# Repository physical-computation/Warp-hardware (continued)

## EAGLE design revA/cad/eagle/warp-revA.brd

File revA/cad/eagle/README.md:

Warp revision A, Eagle CAD files
=========================

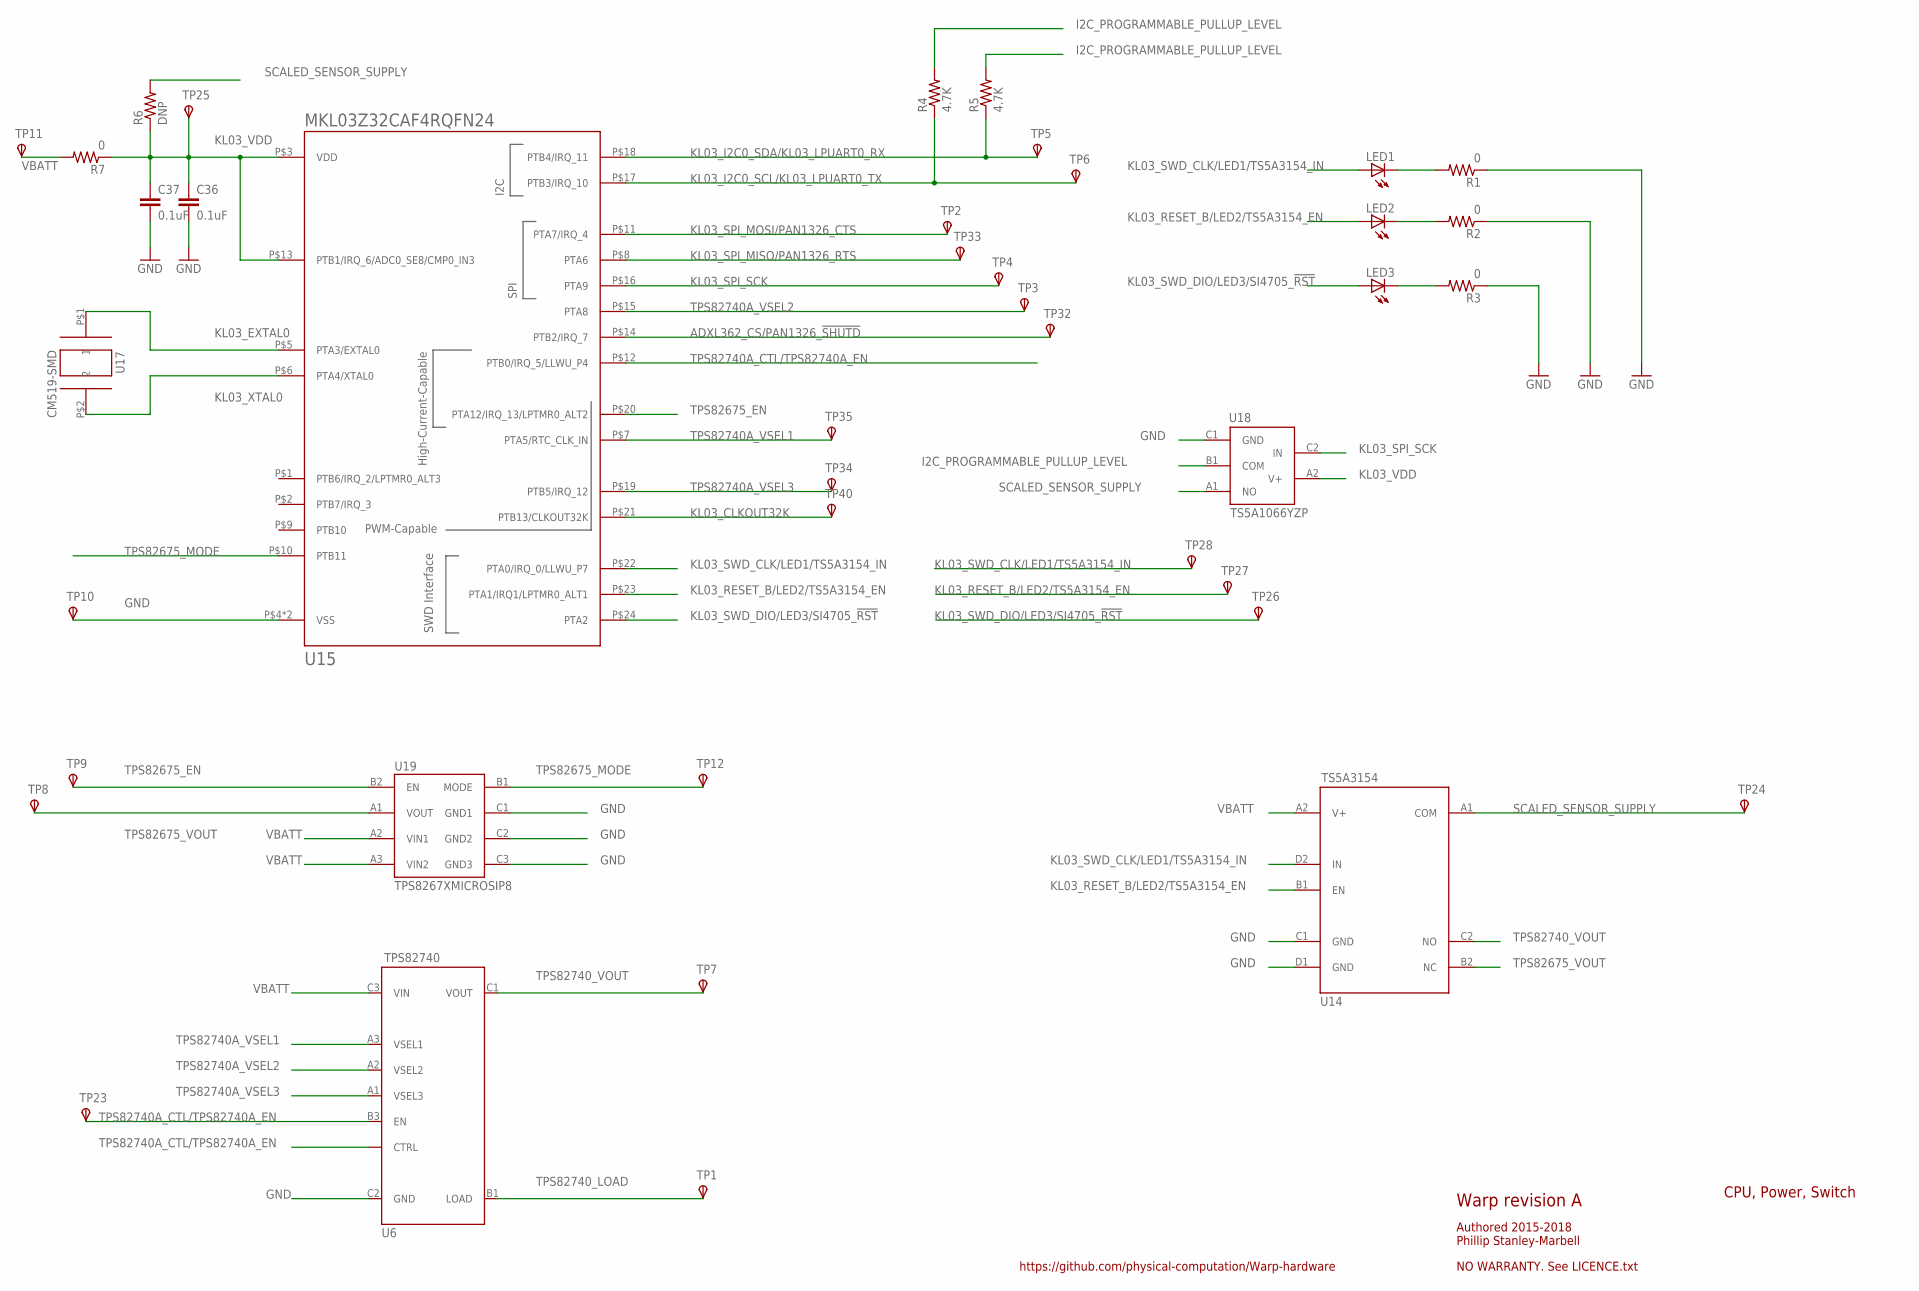
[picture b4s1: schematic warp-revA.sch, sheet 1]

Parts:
C36, C37: 0.1uF; 0402-CAP
LED1, LED2, LED3: LEDSML0603; SML0603
R1, R2, R3, R7: 0; 0402-RES
R4, R5: 4.7K; 0402-RES
R6: DNP; 0402-RES
TP1, TP2, TP3, TP4, TP5, TP6, TP7, TP8, TP9, TP10, TP11, TP12, TP23, TP24, TP25, TP26, TP27, TP28, TP32, TP33, TP34, TP35, TP40: TPSTP06R; TP06R
U6: TPS82740
U14: TS5A3154
U15: MKL03Z32CAF4RQFN24; MKL03Z32VFK4R
U17: CM519-SMD; CM519
U18: TS5A1066YZP; R-XBGA-N5
U19: TPS8267XMICROSIP8; MICROSIP-8

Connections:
ADXL362_CS/PAN1326_!SHUTD: TP32.TP, U15.P$14 (PTB2/IRQ_7); also elsewhere on the board
GND: C36.2, C37.2, R1.1, R2.1, R3.1, TP10.TP, U6.C2 (GND), U14.C1 (GND), U14.D1 (GND), U15.P$4 (VSS), U15.P$PAD (VSS), U18.C1 (GND), U19.C1 (GND1), U19.C2 (GND2), U19.C3 (GND3); also elsewhere on the board
I2C_PROGRAMMABLE_PULLUP_LEVEL: R4.2, R5.2, U18.B1 (COM)
KL03_CLKOUT32K: TP40.TP, U15.P$21 (PTB13/CLKOUT32K); also elsewhere on the board
KL03_EXTAL0: U15.P$5 (PTA3/EXTAL0), U17.P$1 (1)
KL03_I2C0_SCL/KL03_LPUART0_TX: R4.1, TP6.TP, U15.P$17 (PTB3/IRQ_10); also elsewhere on the board
KL03_I2C0_SDA/KL03_LPUART0_RX: R5.1, TP5.TP, U15.P$18 (PTB4/IRQ_11); also elsewhere on the board
KL03_RESET_B/LED2/TS5A3154_EN: LED2.A, TP27.TP, U14.B1 (EN), U15.P$23 (PTA1/IRQ1/LPTMR0_ALT1); also elsewhere on the board
KL03_SPI_MISO/PAN1326_RTS: TP33.TP, U15.P$8 (PTA6); also elsewhere on the board
KL03_SPI_MOSI/PAN1326_CTS: TP2.TP, U15.P$11 (PTA7/IRQ_4); also elsewhere on the board
KL03_SPI_SCK: TP4.TP, U15.P$16 (PTA9), U18.C2 (IN); also elsewhere on the board
KL03_SWD_CLK/LED1/TS5A3154_IN: LED1.A, TP28.TP, U14.D2 (IN), U15.P$22 (PTA0/IRQ_0/LLWU_P7); also elsewhere on the board
KL03_SWD_DIO/LED3/SI4705_!RST: LED3.A, TP26.TP, U15.P$24 (PTA2); also elsewhere on the board
KL03_VDD: C36.1, C37.1, R6.1, R7.1, TP25.TP, U15.P$3 (VDD), U15.P$13 (PTB1/IRQ_6/ADC0_SE8/CMP0_IN3), U18.A2 (V+)
KL03_XTAL0: U15.P$6 (PTA4/XTAL0), U17.P$2 (2)
unnamed: LED1.C, R1.2
unnamed: LED2.C, R2.2
unnamed: LED3.C, R3.2
SCALED_SENSOR_SUPPLY: R6.2, TP24.TP, U14.A1 (COM), U18.A1 (NO); also elsewhere on the board
TPS82675_EN: TP9.TP, U15.P$20 (PTA12/IRQ_13/LPTMR0_ALT2), U19.B2 (EN)
TPS82675_MODE: TP12.TP, U15.P$10 (PTB11), U19.B1 (MODE)
TPS82675_VOUT: TP8.TP, U14.B2 (NC), U19.A1 (VOUT)
TPS82740A_CTL/TPS82740A_EN: TP23.TP, U6.B2 (CTRL), U6.B3 (EN), U15.P$12 (PTB0/IRQ_5/LLWU_P4)
TPS82740A_VSEL1: TP35.TP, U6.A3 (VSEL1), U15.P$7 (PTA5/RTC_CLK_IN)
TPS82740A_VSEL2: TP3.TP, U6.A2 (VSEL2), U15.P$15 (PTA8)
TPS82740A_VSEL3: TP34.TP, U6.A1 (VSEL3), U15.P$19 (PTB5/IRQ_12)
TPS82740_LOAD: TP1.TP, U6.B1 (LOAD)
TPS82740_VOUT: TP7.TP, U6.C1 (VOUT), U14.C2 (NO)
VBATT: R7.2, TP11.TP, U6.C3 (VIN), U14.A2 (V+), U19.A2 (VIN1), U19.A3 (VIN2); also elsewhere on the board

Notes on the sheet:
Warp revision A
Authored 2015-2018 Phillip Stanley-Marbell
NO WARRANTY. See LICENCE.txt
https://github.com/physical-computation/Warp-hardware
CPU, Power, Switch

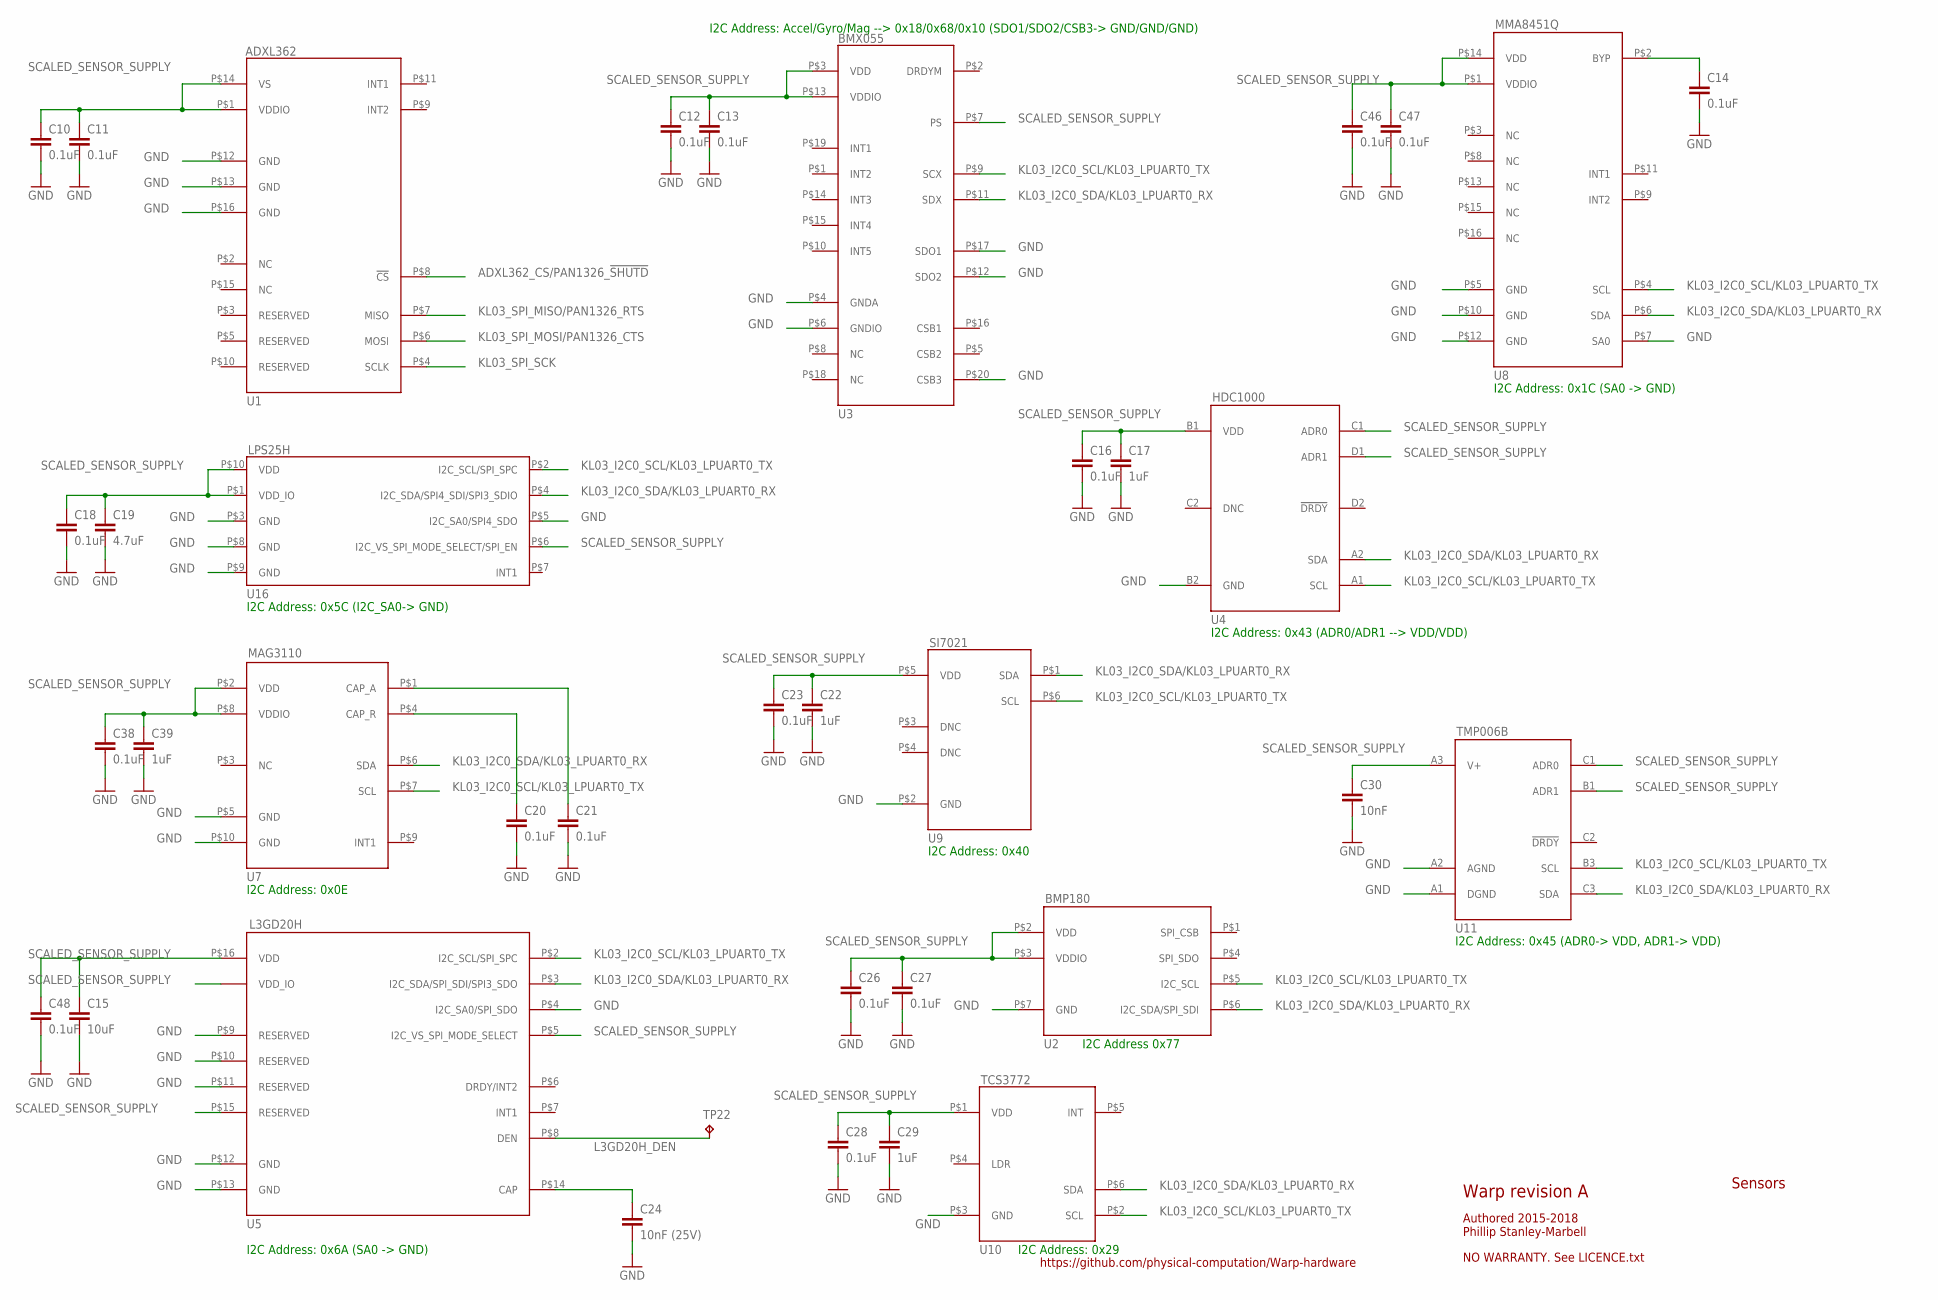
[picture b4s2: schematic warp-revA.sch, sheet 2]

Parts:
C10, C11, C12, C13, C14, C16, C18, C20, C21, C23, C26, C27, C28, C38, C46, C47, C48: 0.1uF; 0402-CAP
C15: 10uF; 0402-CAP
C17, C22, C29, C39: 1uF; 0402-CAP
C19: 4.7uF; 0402-CAP
C24: 10nF (25V); 0402-CAP
C30: 10nF; 0402-CAP
TP22: TPTP06R; TP06R
U1: ADXL362
U2: BMP180
U3: BMX055
U4: HDC1000
U5: L3GD20H
U7: MAG3110
U8: MMA8451Q
U9: SI7021
U10: TCS3772
U11: TMP006B
U16: LPS25H

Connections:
ADXL362_CS/PAN1326_!SHUTD: U1.P$8 (!CS); also elsewhere on the board
GND: C10.2, C11.2, C12.2, C13.2, C14.2, C15.2, C16.2, C17.2, C18.2, C19.2, C20.2, C21.2, C22.2, C23.2, C24.2, C26.2, C27.2, C28.2, C29.2, C30.2, C38.2, C39.2, C46.2, C47.2, C48.2, U1.P$12 (GND), U1.P$13 (GND), U1.P$16 (GND), U2.P$7 (GND), U3.P$4 (GNDA), U3.P$6 (GNDIO), U3.P$12 (SDO2), U3.P$17 (SDO1), U3.P$20 (CSB3), U4.B2 (GND), U5.P$4 (I2C_SA0/SPI_SDO), U5.P$9 (RESERVED), U5.P$10 (RESERVED), U5.P$11 (RESERVED), U5.P$12 (GND), U5.P$13 (GND), U7.P$5 (GND), U7.P$10 (GND), U8.P$5 (GND), U8.P$7 (SA0), U8.P$10 (GND), U8.P$12 (GND), U9.P$2 (GND), U10.P$3 (GND), U11.A1 (DGND), U11.A2 (AGND), U16.P$3 (GND), U16.P$5 (I2C_SA0/SPI4_SDO), U16.P$8 (GND), U16.P$9 (GND); also elsewhere on the board
KL03_I2C0_SCL/KL03_LPUART0_TX: U2.P$5 (I2C_SCL), U3.P$9 (SCX), U4.A1 (SCL), U5.P$2 (I2C_SCL/SPI_SPC), U7.P$7 (SCL), U8.P$4 (SCL), U9.P$6 (SCL), U10.P$2 (SCL), U11.B3 (SCL), U16.P$2 (I2C_SCL/SPI_SPC); also elsewhere on the board
KL03_I2C0_SDA/KL03_LPUART0_RX: U2.P$6 (I2C_SDA/SPI_SDI), U3.P$11 (SDX), U4.A2 (SDA), U5.P$3 (I2C_SDA/SPI_SDI/SPI3_SDO), U7.P$6 (SDA), U8.P$6 (SDA), U9.P$1 (SDA), U10.P$6 (SDA), U11.C3 (SDA), U16.P$4 (I2C_SDA/SPI4_SDI/SPI3_SDIO); also elsewhere on the board
KL03_SPI_MISO/PAN1326_RTS: U1.P$7 (MISO); also elsewhere on the board
KL03_SPI_MOSI/PAN1326_CTS: U1.P$6 (MOSI); also elsewhere on the board
KL03_SPI_SCK: U1.P$4 (SCLK); also elsewhere on the board
L3GD20H_DEN: TP22.TP, U5.P$8 (DEN)
unnamed: C14.1, U8.P$2 (BYP)
unnamed: C21.1, U7.P$1 (CAP_A)
unnamed: C20.1, U7.P$4 (CAP_R)
unnamed: C24.1, U5.P$14 (CAP)
SCALED_SENSOR_SUPPLY: C10.1, C11.1, C12.1, C13.1, C15.1, C16.1, C17.1, C18.1, C19.1, C22.1, C23.1, C26.1, C27.1, C28.1, C29.1, C30.1, C38.1, C39.1, C46.1, C47.1, C48.1, U1.P$1 (VDDIO), U1.P$14 (VS), U2.P$2 (VDD), U2.P$3 (VDDIO), U3.P$3 (VDD), U3.P$7 (PS), U3.P$13 (VDDIO), U4.B1 (VDD), U4.C1 (ADR0), U4.D1 (ADR1), U5.P$1 (VDD_IO), U5.P$5 (I2C_VS_SPI_MODE_SELECT), U5.P$15 (RESERVED), U5.P$16 (VDD), U7.P$2 (VDD), U7.P$8 (VDDIO), U8.P$1 (VDDIO), U8.P$14 (VDD), U9.P$5 (VDD), U10.P$1 (VDD), U11.A3 (V+), U11.B1 (ADR1), U11.C1 (ADR0), U16.P$1 (VDD_IO), U16.P$6 (I2C_VS_SPI_MODE_SELECT/SPI_EN), U16.P$10 (VDD); also elsewhere on the board

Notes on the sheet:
I2C Address: 0x1C (SA0 -> GND)
I2C Address: Accel/Gyro/Mag --> 0x18/0x68/0x10 (SDO1/SDO2/CSB3-> GND/GND/GND)
I2C Address: 0x43 (ADR0/ADR1 --> VDD/VDD)
I2C Address: 0x5C (I2C_SA0-> GND)
I2C Address: 0x0E
I2C Address: 0x40
I2C Address: 0x6A (SA0 -> GND)
I2C Address 0x77
I2C Address: 0x29
I2C Address: 0x45 (ADR0-> VDD, ADR1-> VDD)
Warp revision A
Authored 2015-2018 Phillip Stanley-Marbell
NO WARRANTY. See LICENCE.txt
https://github.com/physical-computation/Warp-hardware
Sensors

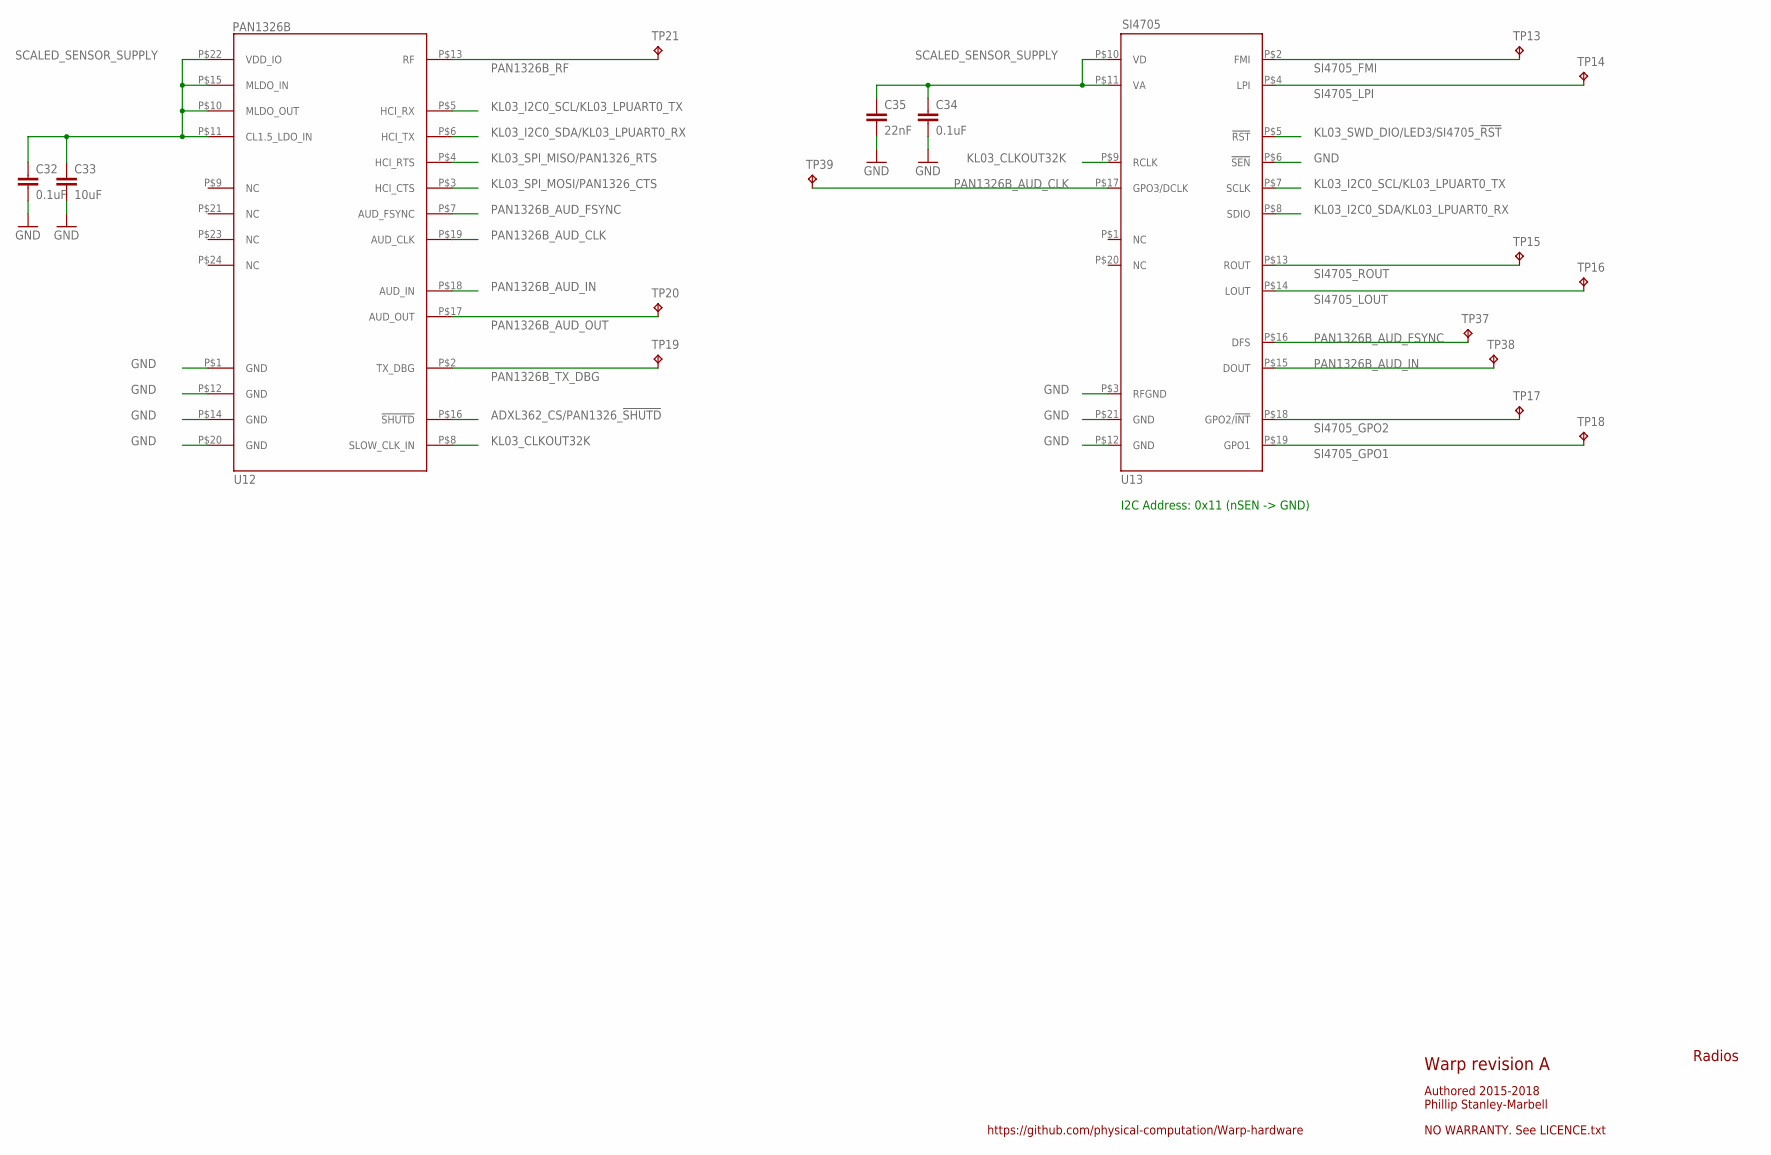
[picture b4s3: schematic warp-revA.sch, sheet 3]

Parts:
C32, C34: 0.1uF; 0402-CAP
C33: 10uF; 0402-CAP
C35: 22nF; 0402-CAP
TP13, TP14, TP15, TP16, TP17, TP18, TP19, TP20, TP21, TP37, TP38, TP39: TPTP06R; TP06R
U12: PAN1326B
U13: SI4705

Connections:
ADXL362_CS/PAN1326_!SHUTD: U12.P$16 (!SHUTD); also elsewhere on the board
GND: C32.2, C33.2, C34.2, C35.2, U12.P$1 (GND), U12.P$12 (GND), U12.P$14 (GND), U12.P$20 (GND), U13.P$3 (RFGND), U13.P$6 (!SEN), U13.P$12 (GND), U13.P$21 (GND); also elsewhere on the board
KL03_CLKOUT32K: U12.P$8 (SLOW_CLK_IN), U13.P$9 (RCLK); also elsewhere on the board
KL03_I2C0_SCL/KL03_LPUART0_TX: U12.P$5 (HCI_RX), U13.P$7 (SCLK); also elsewhere on the board
KL03_I2C0_SDA/KL03_LPUART0_RX: U12.P$6 (HCI_TX), U13.P$8 (SDIO); also elsewhere on the board
KL03_SPI_MISO/PAN1326_RTS: U12.P$4 (HCI_RTS); also elsewhere on the board
KL03_SPI_MOSI/PAN1326_CTS: U12.P$3 (HCI_CTS); also elsewhere on the board
KL03_SWD_DIO/LED3/SI4705_!RST: U13.P$5 (!RST); also elsewhere on the board
PAN1326B_AUD_CLK: TP39.TP, U12.P$19 (AUD_CLK), U13.P$17 (GPO3/DCLK)
PAN1326B_AUD_FSYNC: TP37.TP, U12.P$7 (AUD_FSYNC), U13.P$16 (DFS)
PAN1326B_AUD_IN: TP38.TP, U12.P$18 (AUD_IN), U13.P$15 (DOUT)
PAN1326B_AUD_OUT: TP20.TP, U12.P$17 (AUD_OUT)
PAN1326B_RF: TP21.TP, U12.P$13 (RF)
PAN1326B_TX_DBG: TP19.TP, U12.P$2 (TX_DBG)
SCALED_SENSOR_SUPPLY: C32.1, C33.1, C34.1, C35.1, U12.P$10 (MLDO_OUT), U12.P$11 (CL1.5_LDO_IN), U12.P$15 (MLDO_IN), U12.P$22 (VDD_IO), U13.P$10 (VD), U13.P$11 (VA); also elsewhere on the board
SI4705_FMI: TP13.TP, U13.P$2 (FMI)
SI4705_GPO1: TP18.TP, U13.P$19 (GPO1)
SI4705_GPO2: TP17.TP, U13.P$18 (GPO2/!INT)
SI4705_LOUT: TP16.TP, U13.P$14 (LOUT)
SI4705_LPI: TP14.TP, U13.P$4 (LPI)
SI4705_ROUT: TP15.TP, U13.P$13 (ROUT)

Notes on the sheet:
I2C Address: 0x11 (nSEN -> GND)
Warp revision A
Authored 2015-2018 Phillip Stanley-Marbell
NO WARRANTY. See LICENCE.txt
https://github.com/physical-computation/Warp-hardware
Radios

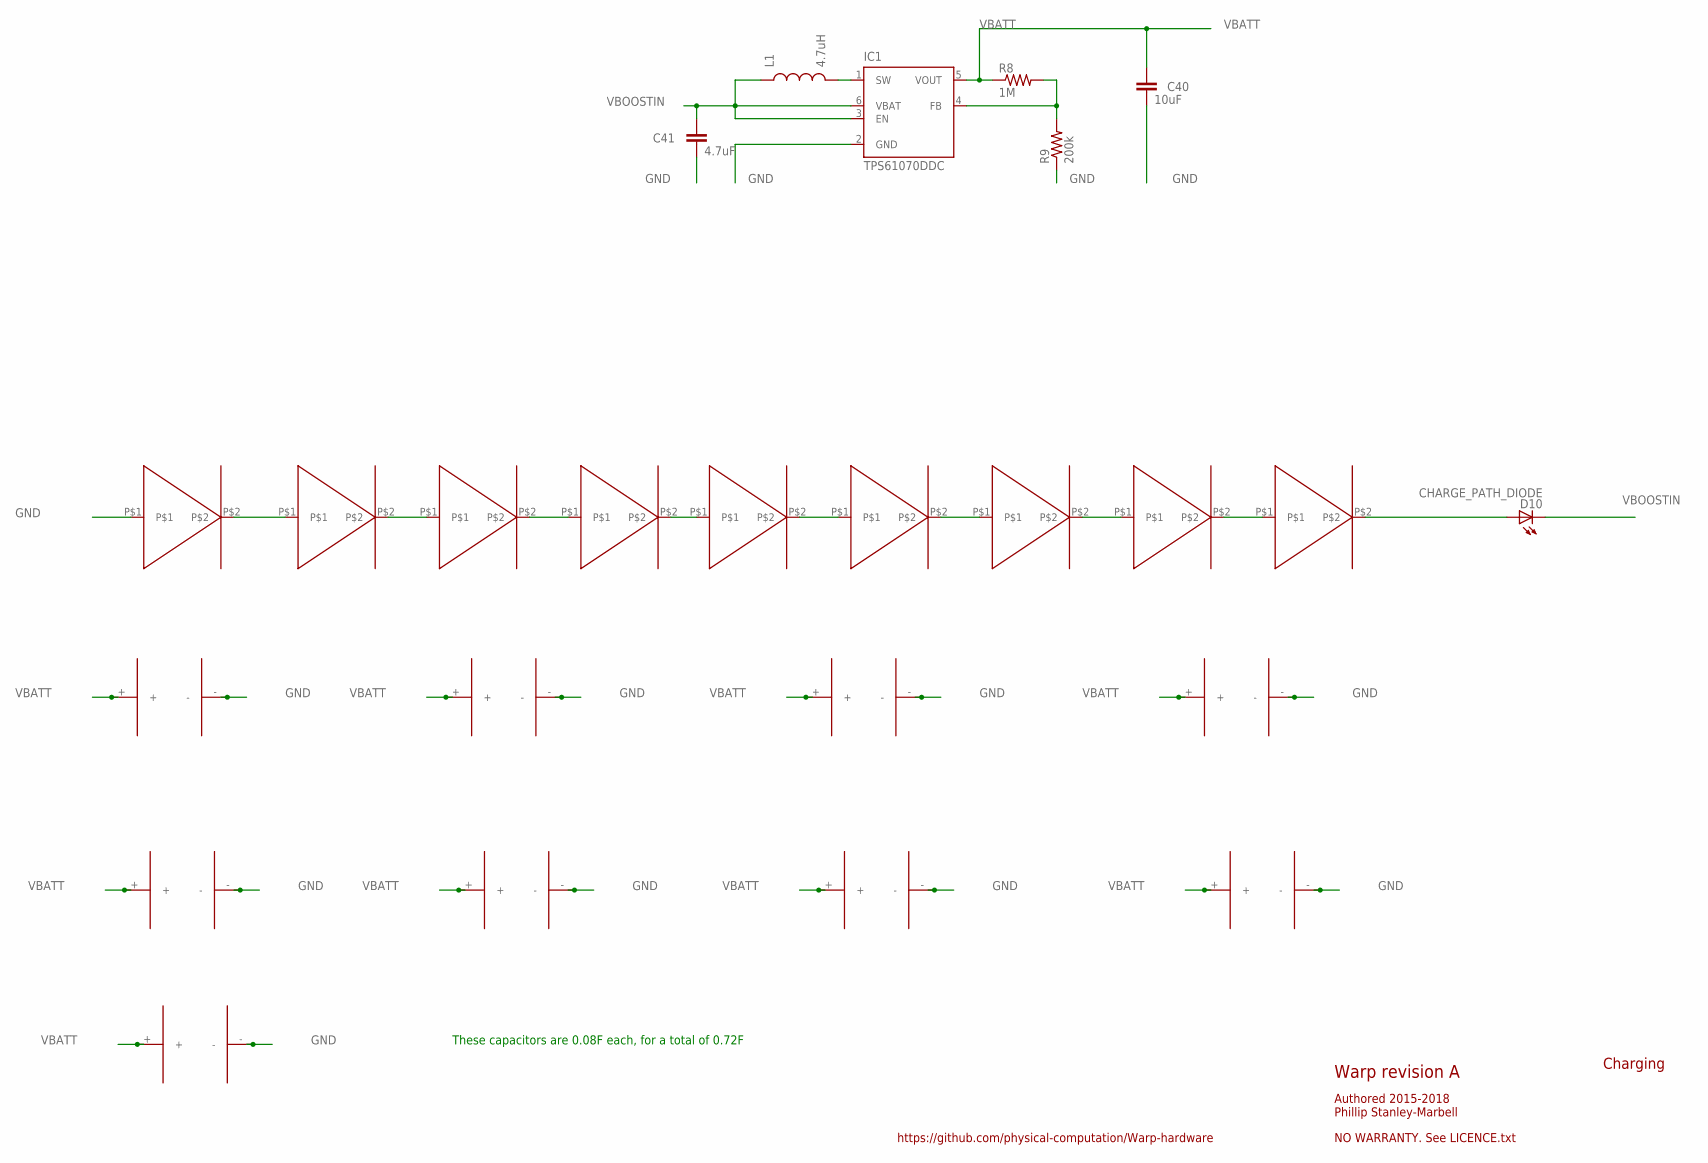
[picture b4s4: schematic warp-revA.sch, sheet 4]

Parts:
C1, C2, C3, C4, C5, C6, C7, C8, C9: XH414HGIV01E
C40: 10uF; 0402-CAP
C41: 4.7uF; 0402-CAP
D1, D2, D3, D4, D5, D6, D7, D8, D9: TEMD5080
D10: CHARGE_PATH_DIODE; SML0603
IC1: TPS61070DDC; TSOT23-6_DDC
L1: 4.7uH; 0603
R8: 1M; 0402-RES
R9: 200k; 0402-RES

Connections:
GND: C1.-, C2.-, C3.-, C4.-, C5.-, C6.-, C7.-, C8.-, C9.-, C40.2, C41.2, D1.P$1, IC1.2 (GND), R9.1; also elsewhere on the board
unnamed: IC1.1 (SW), L1.2
unnamed: IC1.4 (FB), R8.2, R9.2
unnamed: D1.P$2, D2.P$1
unnamed: D2.P$2, D3.P$1
unnamed: D3.P$2, D4.P$1
unnamed: D4.P$2, D5.P$1
unnamed: D5.P$2, D6.P$1
unnamed: D6.P$2, D7.P$1
unnamed: D7.P$2, D8.P$1
unnamed: D8.P$2, D9.P$1
unnamed: D9.P$2, D10.A
VBATT: C1.+, C2.+, C3.+, C4.+, C5.+, C6.+, C7.+, C8.+, C9.+, C40.1, IC1.5 (VOUT), R8.1; also elsewhere on the board
VBOOSTIN: C41.1, D10.C, IC1.3 (EN), IC1.6 (VBAT), L1.1

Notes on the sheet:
These capacitors are 0.08F each, for a total of 0.72F
Warp revision A
Authored 2015-2018 Phillip Stanley-Marbell
NO WARRANTY. See LICENCE.txt
https://github.com/physical-computation/Warp-hardware
Charging

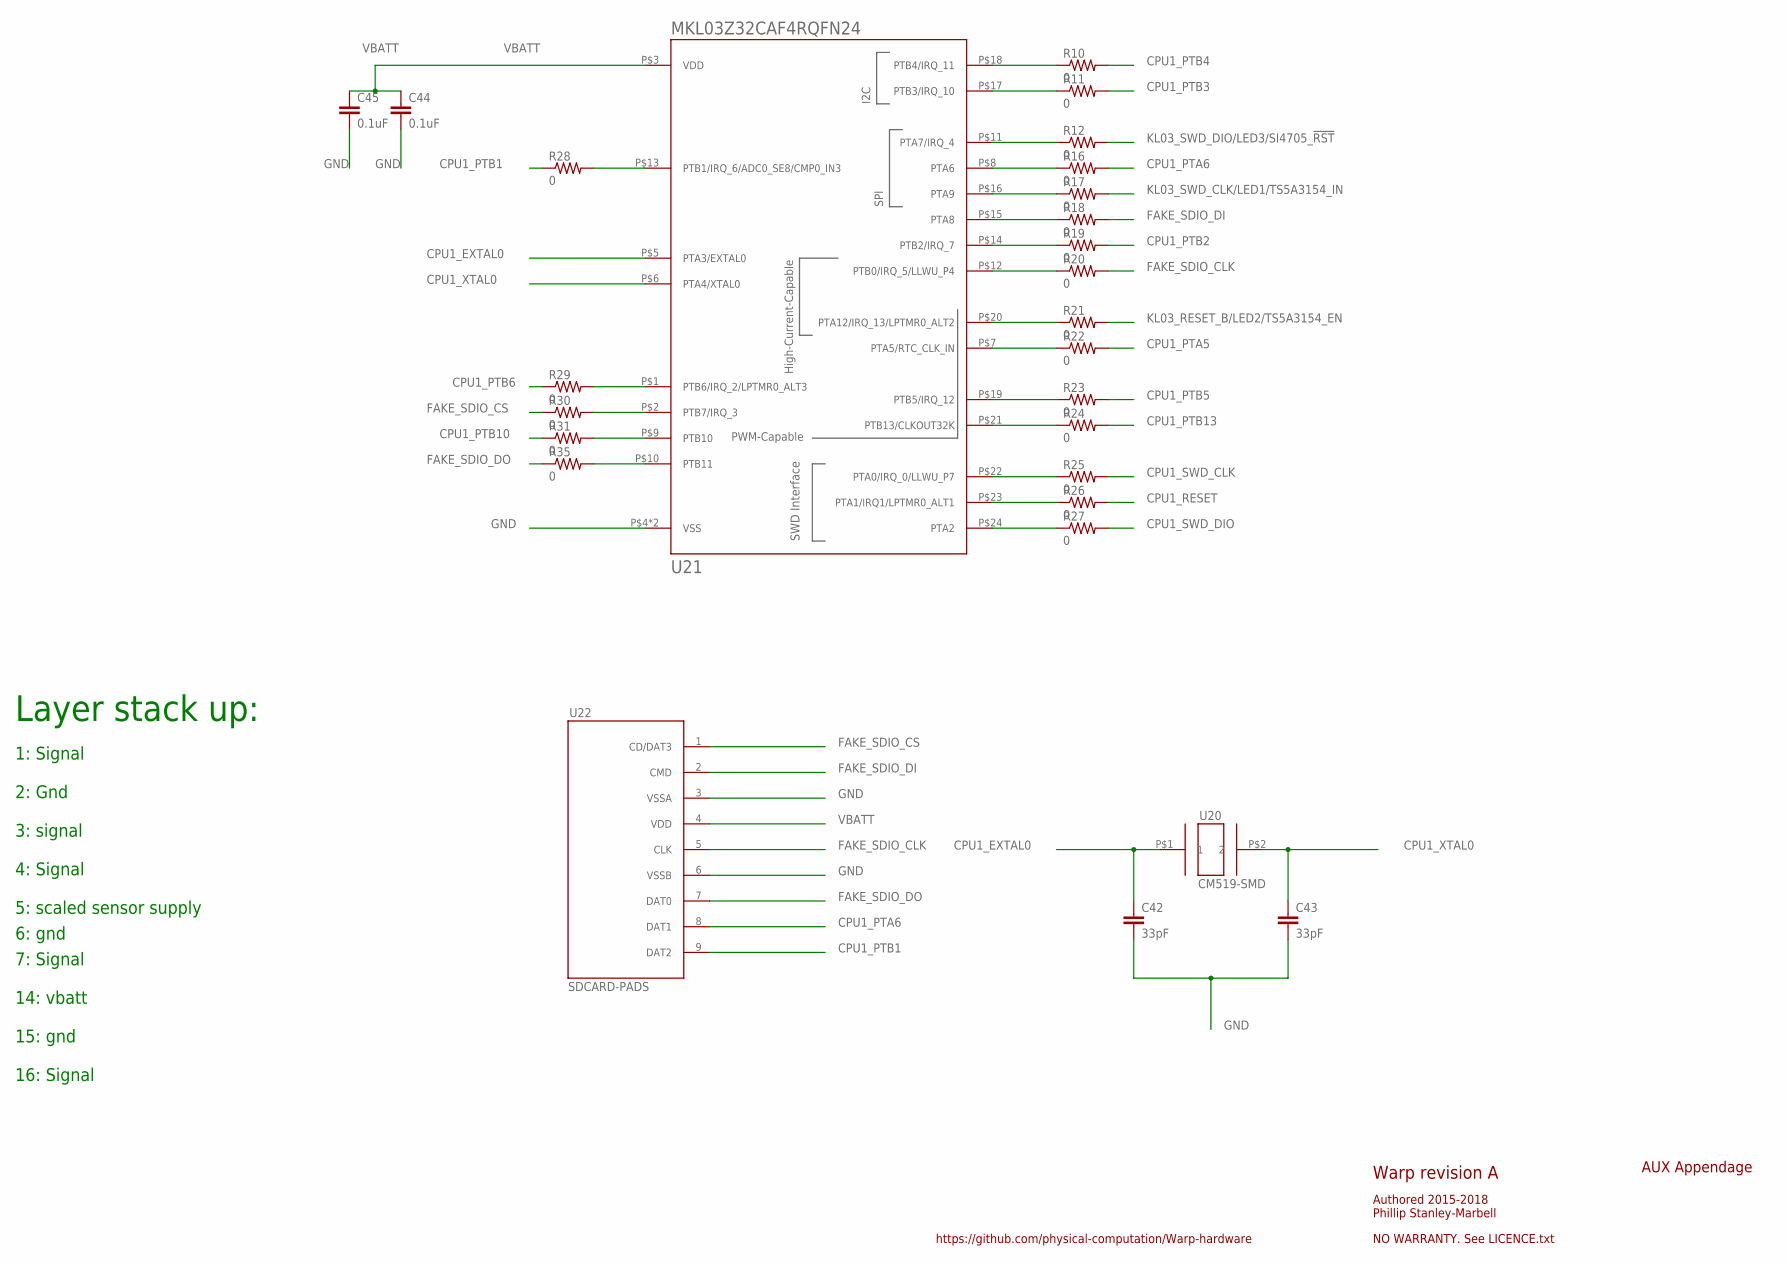
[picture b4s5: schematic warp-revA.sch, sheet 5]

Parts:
C42, C43: 33pF; 0402-CAP
C44, C45: 0.1uF; 0402-CAP
R10, R11, R12, R16, R17, R18, R19, R20, R21, R22, R23, R24, R25, R26, R27, R28, R29, R30, R31, R35: 0; 0402-RES
U20: CM519-SMD; CM519
U21: MKL03Z32CAF4RQFN24; MKL03Z32VFK4R
U22: SDCARD-PADS

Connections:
CPU1_EXTAL0: C42.1, U20.P$1 (1), U21.P$5 (PTA3/EXTAL0)
CPU1_PTA5: R22.2
CPU1_PTA6: R16.2, U22.8 (DAT1)
CPU1_PTB1: R28.1, U22.9 (DAT2)
CPU1_PTB2: R19.2
CPU1_PTB3: R11.2
CPU1_PTB4: R10.2
CPU1_PTB5: R23.2
CPU1_PTB6: R29.1
CPU1_PTB10: R31.1
CPU1_PTB13: R24.2
CPU1_RESET: R26.2
CPU1_SWD_CLK: R25.2
CPU1_SWD_DIO: R27.2
CPU1_XTAL0: C43.1, U20.P$2 (2), U21.P$6 (PTA4/XTAL0)
FAKE_SDIO_CLK: R20.2, U22.5 (CLK)
FAKE_SDIO_CS: R30.1, U22.1 (CD/DAT3)
FAKE_SDIO_DI: R18.2, U22.2 (CMD)
FAKE_SDIO_DO: R35.1, U22.7 (DAT0)
GND: C42.2, C43.2, C44.2, C45.2, U21.P$4 (VSS), U21.P$PAD (VSS), U22.3 (VSSA), U22.6 (VSSB); also elsewhere on the board
KL03_RESET_B/LED2/TS5A3154_EN: R21.2; also elsewhere on the board
KL03_SWD_CLK/LED1/TS5A3154_IN: R17.2; also elsewhere on the board
KL03_SWD_DIO/LED3/SI4705_!RST: R12.2; also elsewhere on the board
unnamed: R28.2, U21.P$13 (PTB1/IRQ_6/ADC0_SE8/CMP0_IN3)
unnamed: R29.2, U21.P$1 (PTB6/IRQ_2/LPTMR0_ALT3)
unnamed: R30.2, U21.P$2 (PTB7/IRQ_3)
unnamed: R31.2, U21.P$9 (PTB10)
unnamed: R35.2, U21.P$10 (PTB11)
unnamed: R10.1, U21.P$18 (PTB4/IRQ_11)
unnamed: R11.1, U21.P$17 (PTB3/IRQ_10)
unnamed: R12.1, U21.P$11 (PTA7/IRQ_4)
unnamed: R16.1, U21.P$8 (PTA6)
unnamed: R17.1, U21.P$16 (PTA9)
unnamed: R18.1, U21.P$15 (PTA8)
unnamed: R19.1, U21.P$14 (PTB2/IRQ_7)
unnamed: R20.1, U21.P$12 (PTB0/IRQ_5/LLWU_P4)
unnamed: R21.1, U21.P$20 (PTA12/IRQ_13/LPTMR0_ALT2)
unnamed: R22.1, U21.P$7 (PTA5/RTC_CLK_IN)
unnamed: R23.1, U21.P$19 (PTB5/IRQ_12)
unnamed: R24.1, U21.P$21 (PTB13/CLKOUT32K)
unnamed: R25.1, U21.P$22 (PTA0/IRQ_0/LLWU_P7)
unnamed: R26.1, U21.P$23 (PTA1/IRQ1/LPTMR0_ALT1)
unnamed: R27.1, U21.P$24 (PTA2)
VBATT: C44.1, C45.1, U21.P$3 (VDD), U22.4 (VDD); also elsewhere on the board

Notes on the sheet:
Layer stack up:
1: Signal
2: Gnd
3: signal
14: vbatt
15: gnd
16: Signal
4: Signal
5: scaled sensor supply
6: gnd
7: Signal
Warp revision A
Authored 2015-2018 Phillip Stanley-Marbell
NO WARRANTY. See LICENCE.txt
https://github.com/physical-computation/Warp-hardware
AUX Appendage

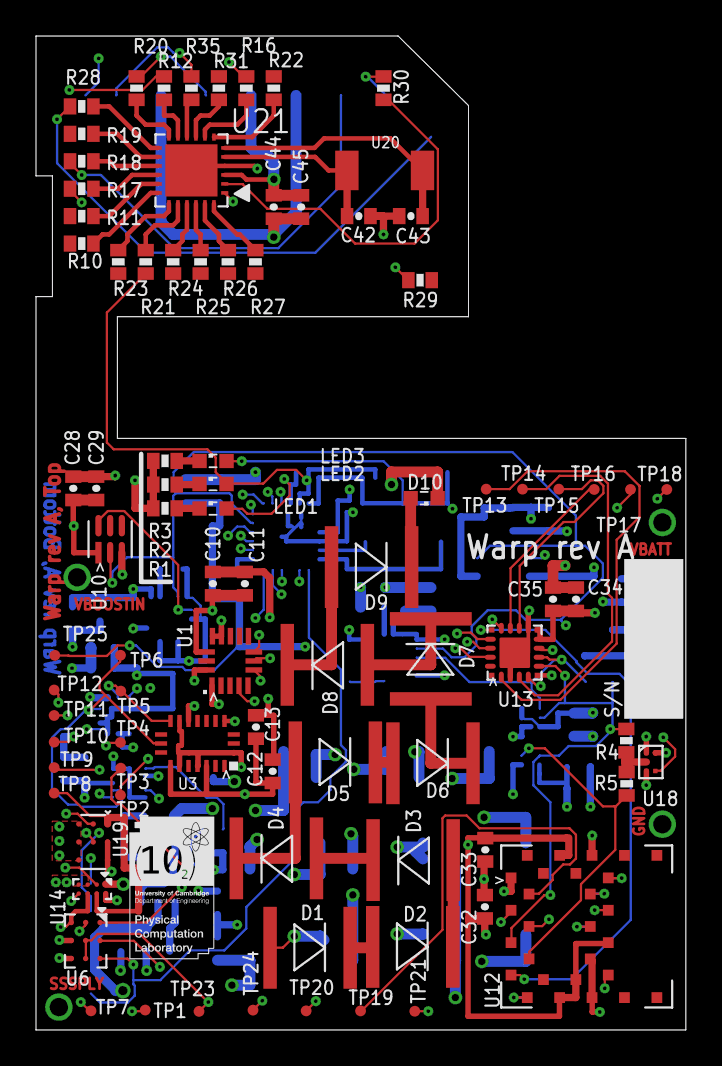
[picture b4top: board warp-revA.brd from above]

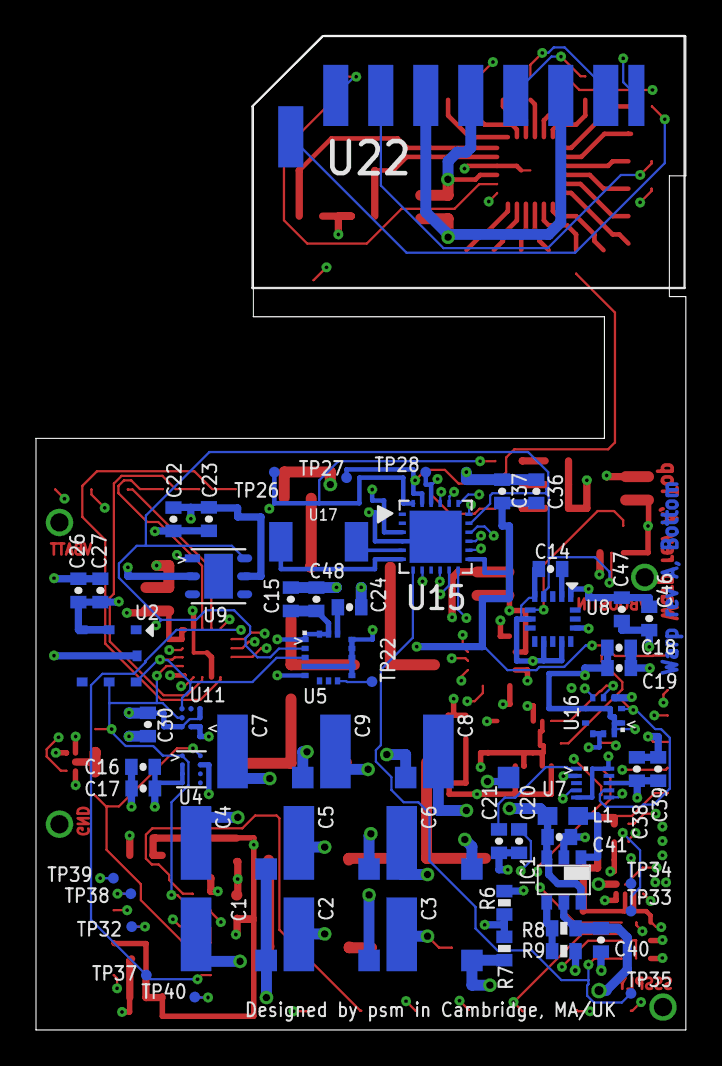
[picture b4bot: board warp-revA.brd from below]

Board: 10 copper layers, 36.1 x 55.2 mm, 148 parts (61 on the bottom side), 86 nets.

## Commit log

2018-05-21 Initial tree stubs
2018-05-25 Basic files for release of revA
2018-05-25 Cleanup
2018-05-25 Architecture image
2018-05-25 Implementation and debug image
2018-05-25 Cleanup debug interface figure for README.md
2018-06-17 Added Fusion360 CAD file
2018-06-22 improved design
2018-06-22 draft design
2018-06-25 included snap design
2018-06-26 add more snaps design to the enclosure
2018-06-28 issue should be solved now
2018-06-28 Enclosure pictures
2018-06-29 Mechanical design for revB
2018-07-03 first draft
2018-07-03 add switch design
2018-07-06 Enclosure design
2018-07-06 Switch design
2018-07-06 file added
2018-07-06 Directory cleanup
2018-07-09 Changes in design
2018-07-10 Add Square enclosures
2018-07-10 Changes to the switch design
2018-07-17 Added datasheets for revA
2018-08-01 Modified version
2018-08-01 Moved Revised-Enclosure-Design-revB.f3d -> Enclosure-Design-RevB.f3d
2018-08-08 Datasheets added
    adding datasheets
2018-08-08 Change of BOM
    adding a column stating details
2018-08-08 Updated changed of BOM
2018-08-08 File modified
2018-08-09 Added wristband design
2019-05-29 Initial import of revision B design.
2019-07-18 solved power issues and added RV8803 support
2019-07-19 Corrected DRC errors, added FT4222 power switch
2019-07-24 Added datasheets for revB
2019-08-29 Layout of charger, boost, reg
2019-08-30 FPGA layout
2019-09-06 Top layout 70% complete
2019-09-11 Top layout removed USE SPI IC
2019-09-13 Start of bottom layer sensor routing
2019-09-14 Bottom sensor placement
2019-09-19 All chips routed
2019-10-07 Corrected DRC errors with layout and completed silkscreen
2019-10-08 Update README.md
    Fixing switches
2019-10-08 Readded revB files and created revC folder
2019-10-09 Added revC eagle files using new fork
2019-10-16 Adding how to power with a SMU
2019-10-18 Added revC branch for Richards incoming PR
2019-11-08 Removed FPGA microvias and rerouted
2019-11-14 MAG3110 with FXOS8700CQ. Added BOM
2019-12-20 Corrected footprint errors
2020-01-07 Corrections to footprints
2020-02-10 Commit of CAD design, BOM and datasheets for 1st production run of Warp-revC
2020-12-10 Added updated BME680 datasheet
2021-09-26 Tree cleanup
